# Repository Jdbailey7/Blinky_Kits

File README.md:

# Blinky_Kits
LED Blinky Soldering Kits

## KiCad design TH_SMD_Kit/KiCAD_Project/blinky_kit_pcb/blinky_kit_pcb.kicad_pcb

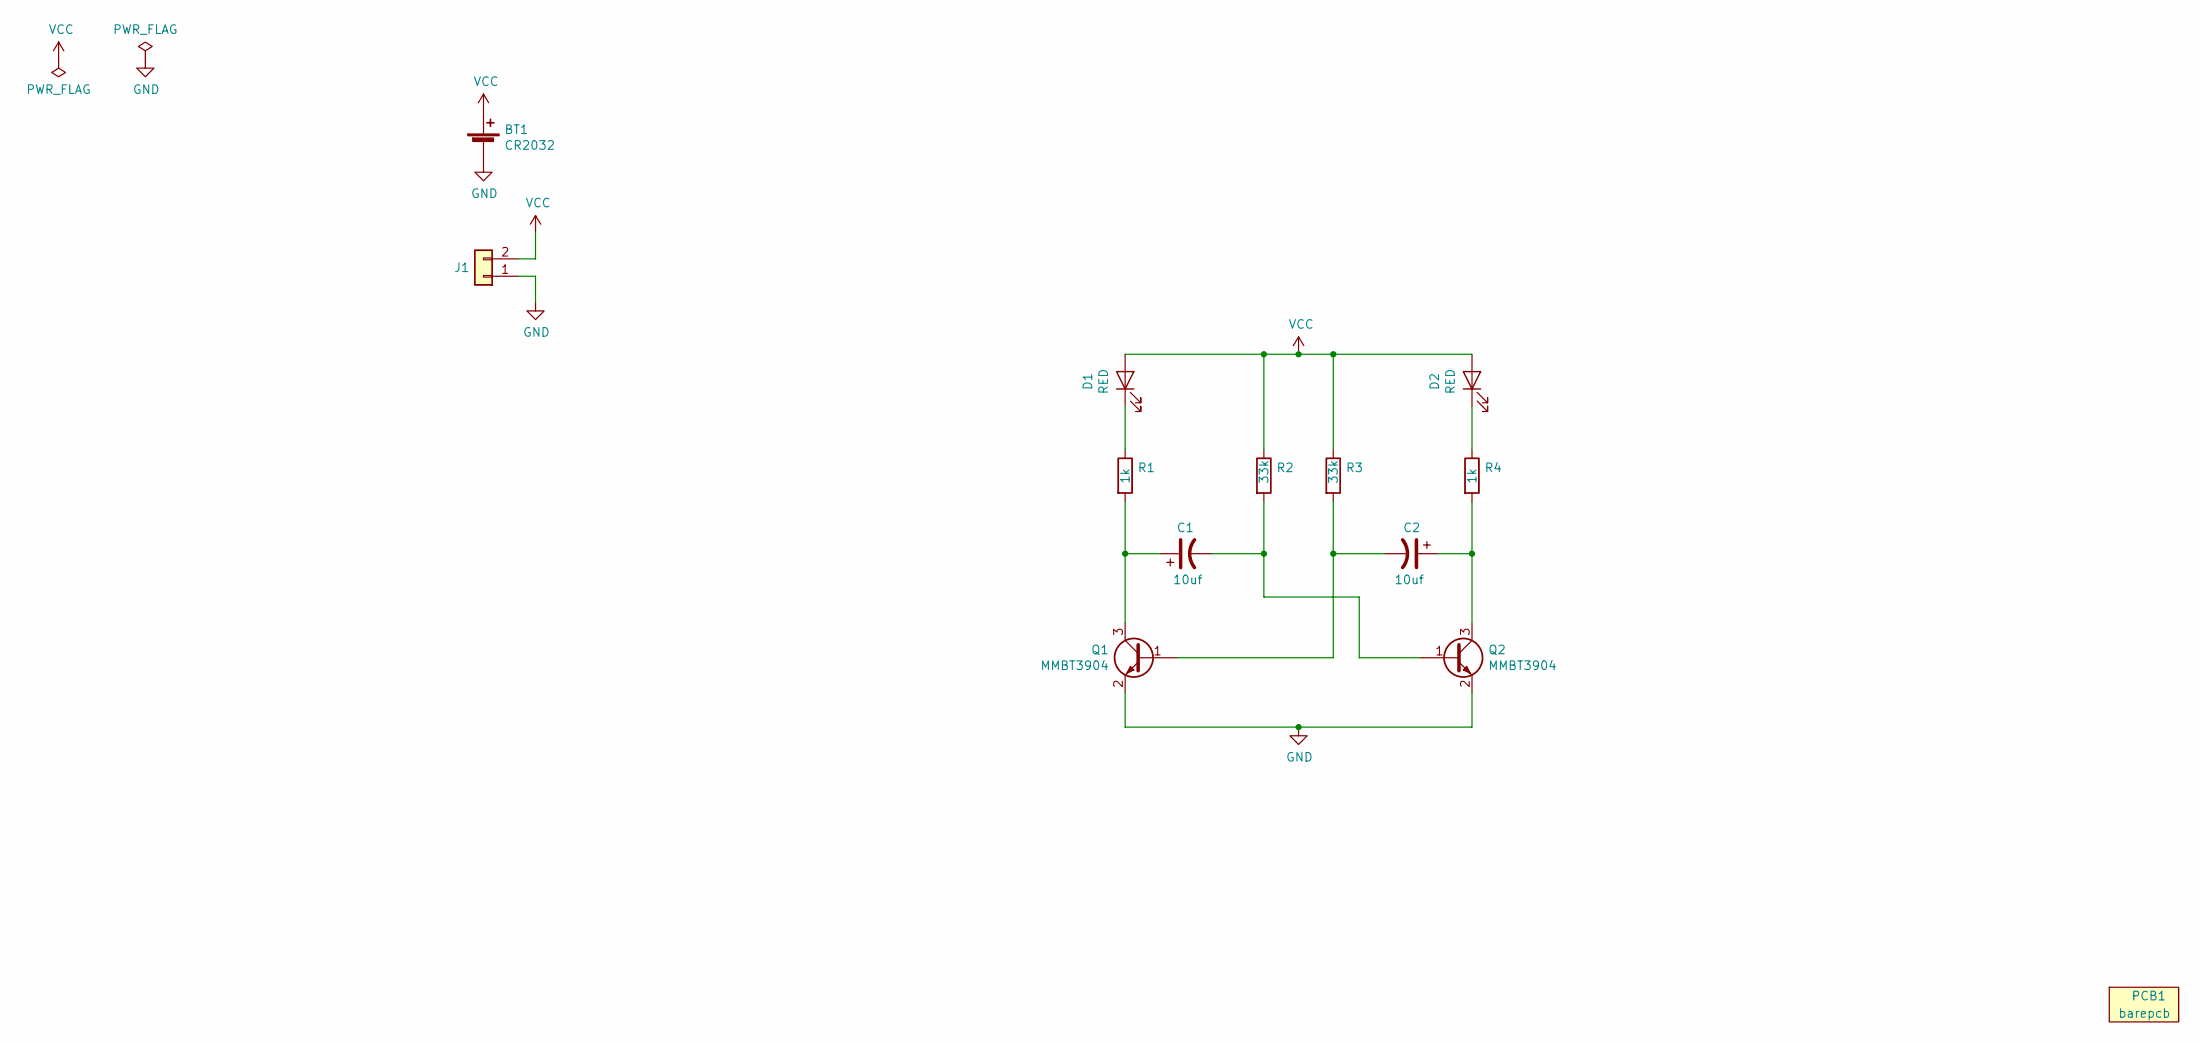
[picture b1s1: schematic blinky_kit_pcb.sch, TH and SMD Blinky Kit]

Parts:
BT1: 1-0000494
C1, C2: 1-0000853
D1, D2: 1-0000568
J1: 2 Pos; SolderWire-0.5sqmm_1x02_P4.6mm_D0.9mm_OD2.1mm_Relief
PCB1: barepcb
Q1, Q2: 1-0000036
R1, R4: 1-0000551
R2, R3: 1-0000548

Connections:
GND: BT1.2 (-), J1.1, Q1.2 (E), Q2.2 (E)
unnamed: C1.1, Q1.3 (C), R1.2
unnamed: C1.2, Q2.1 (B), R2.2
unnamed: C2.1, Q2.3 (C), R4.2
unnamed: C2.2, Q1.1 (B), R3.2
unnamed: D1.1 (K), R1.1
unnamed: D2.1 (K), R4.1
VCC: BT1.1 (+), D1.2 (A), D2.2 (A), J1.2, R2.1, R3.1

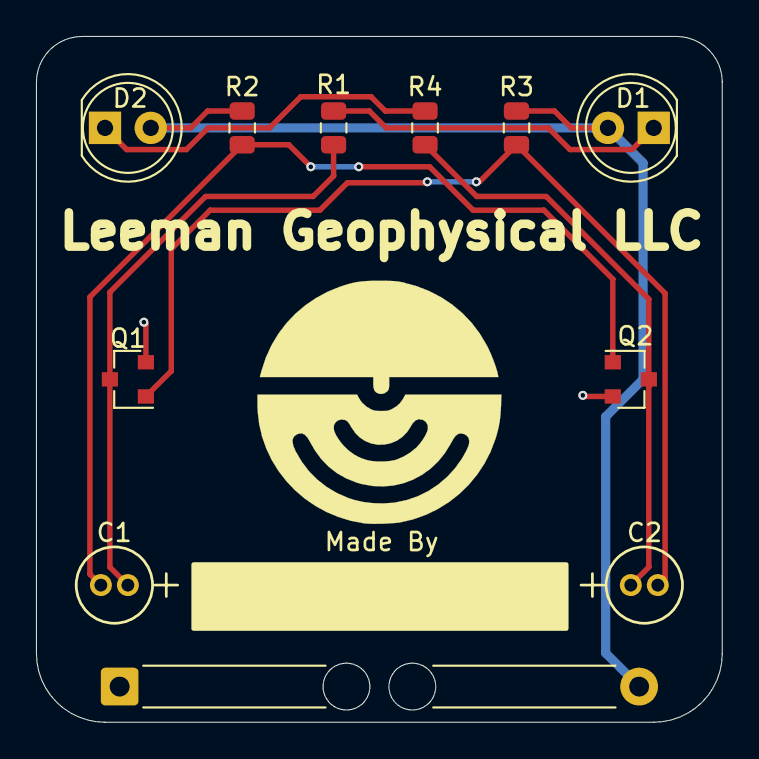
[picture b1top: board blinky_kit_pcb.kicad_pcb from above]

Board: 2 copper layers, 38.1 x 38.1 mm, 13 parts (1 on the bottom side), 8 nets.

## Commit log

2021-04-15 Add draft of schematic
2021-04-15 Initial Layout
2021-04-15 Fix schematic
2021-04-16 Add made by line
2021-04-21 Changed NP connector
2021-04-22 TH and SMD Rev 1.0 Production
2021-05-04 Add Stencil Folder and file

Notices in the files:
parts and their libraries:
Copyright 2016 Accelerated Designs. All rights reserved.
